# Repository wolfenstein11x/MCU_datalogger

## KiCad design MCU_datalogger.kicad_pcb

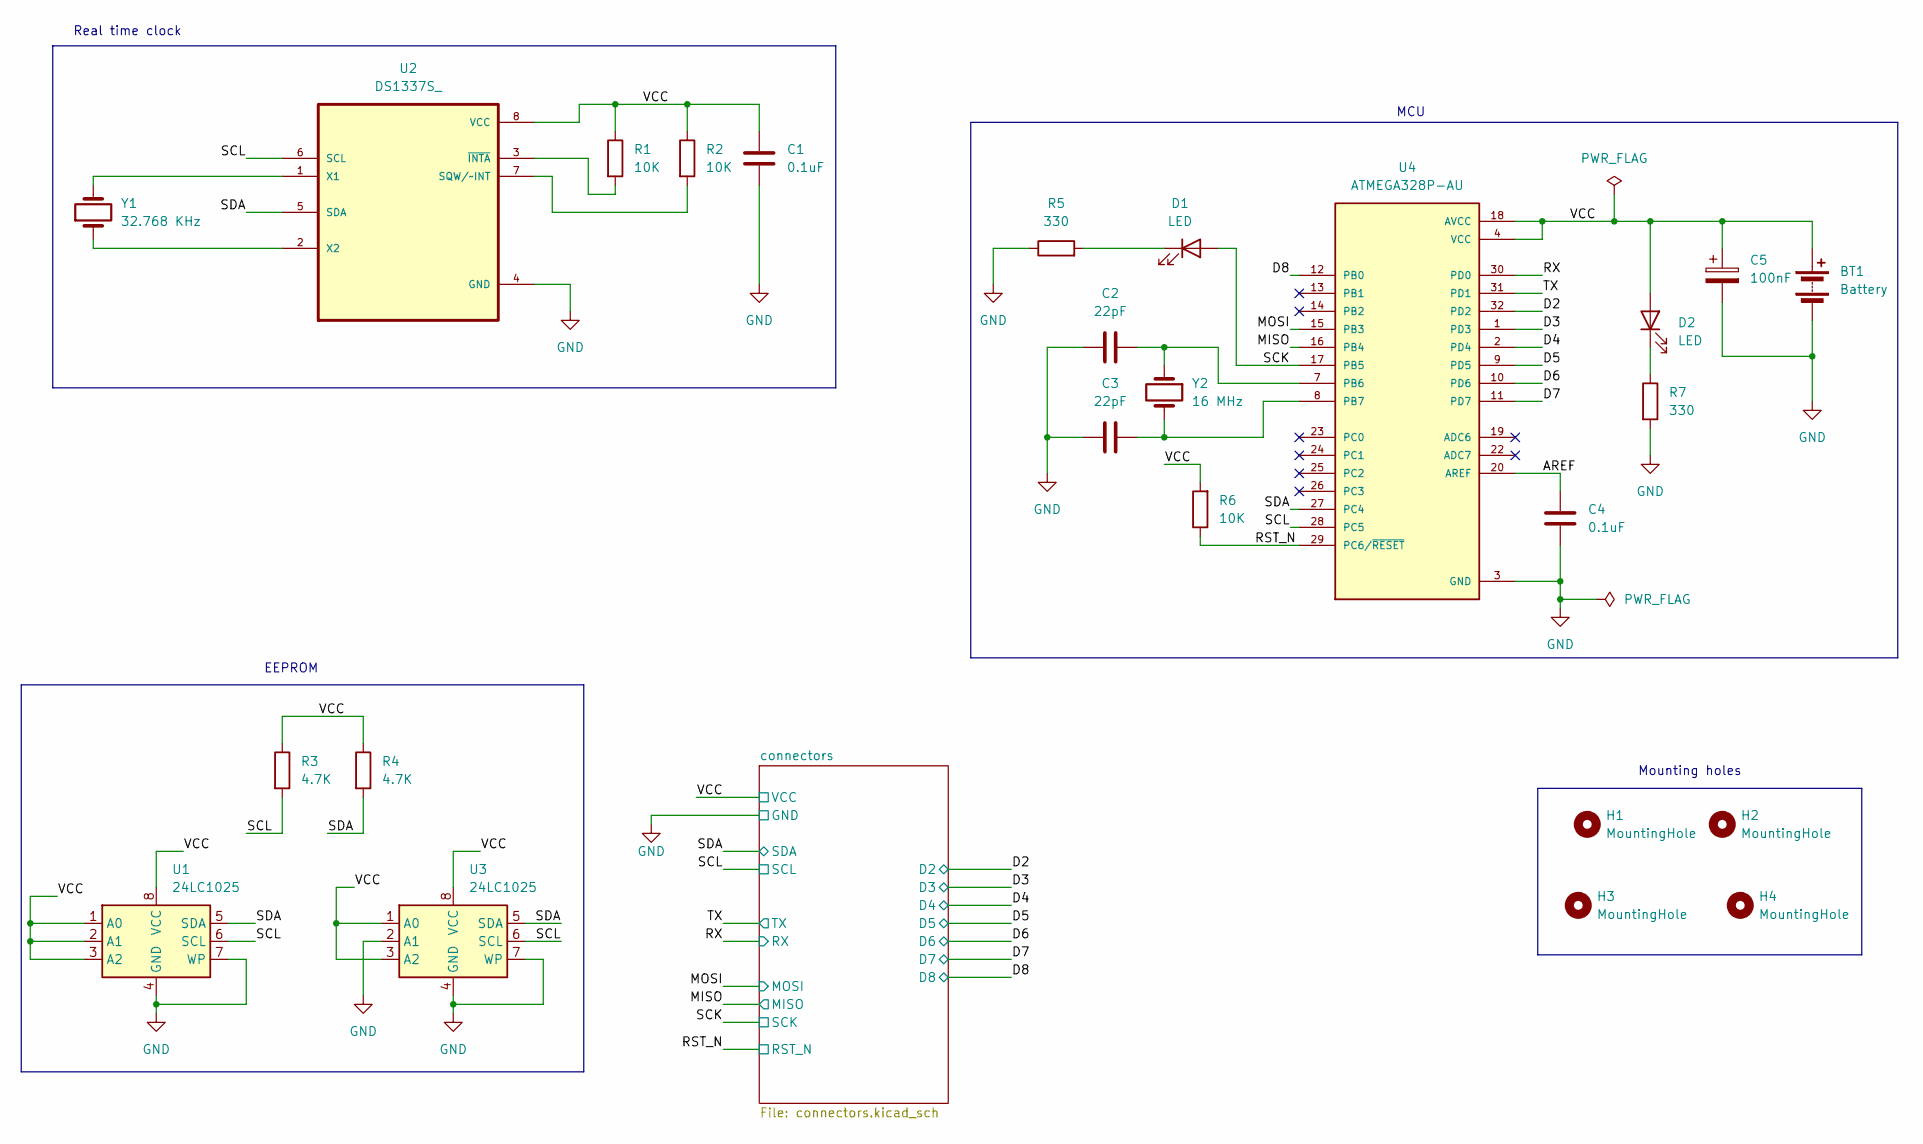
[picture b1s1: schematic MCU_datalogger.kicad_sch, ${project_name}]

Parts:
BT1: Battery; PinHeader_1x02_P2.54mm_Vertical
C1, C4: 0.1uF; C_0805_2012Metric
C2, C3: 22pF; C_0805_2012Metric
C5: 100nF; C_0805_2012Metric
D1, D2: LED; LED_0805_2012Metric
H1, H2, H3, H4: MountingHole; MountingHole_2.1mm
R1, R2, R6: 10K; R_0805_2012Metric
R3, R4: 4.7K; R_0805_2012Metric
R5, R7: 330; R_0805_2012Metric
U1, U3: 24LC1025; SOIC-8_5.23x5.23mm_P1.27mm
U2: DS1337S_; SOIC127P600X175-8N
U4: ATMEGA328P-AU; QFP80P900X900X120-32N; PARTREV 8271A
Y1: 32.768 KHz; Crystal_SMD_5032-2Pin_5.0x3.2mm_HandSoldering
Y2: 16 MHz; Crystal_SMD_5032-2Pin_5.0x3.2mm_HandSoldering

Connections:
/AREF: C4.2, U4.20 (AREF)
/D2: U4.32 (PD2); also elsewhere on the board
/D3: U4.1 (PD3); also elsewhere on the board
/D4: U4.2 (PD4); also elsewhere on the board
/D5: U4.9 (PD5); also elsewhere on the board
/D6: U4.10 (PD6); also elsewhere on the board
/D7: U4.11 (PD7); also elsewhere on the board
/D8: U4.12 (PB0); also elsewhere on the board
/MISO: U4.16 (PB4); also elsewhere on the board
/MOSI: U4.15 (PB3); also elsewhere on the board
/RST_N: R6.1, U4.29 (PC6/~RESET); also elsewhere on the board
/RX: U4.30 (PD0); also elsewhere on the board
/SCK: D1.2 (A), U4.17 (PB5); also elsewhere on the board
/SCL: R3.2, U1.6 (SCL), U2.6 (SCL), U3.6 (SCL), U4.28 (PC5); also elsewhere on the board
/SDA: R4.2, U1.5 (SDA), U2.5 (SDA), U3.5 (SDA), U4.27 (PC4); also elsewhere on the board
/TX: U4.31 (PD1); also elsewhere on the board
GND: BT1.2 (-), C1.2, C2.1, C3.1, C4.1, C5.2, R5.1, R7.2, U1.4 (GND), U1.7 (WP), U2.4 (GND), U3.2 (A1), U3.4 (GND), U3.7 (WP), U4.3 (GND), U4.5 (GND), U4.21 (GND); also elsewhere on the board
unnamed: D1.1 (K), R5.2
unnamed: D2.1 (K), R7.1
unnamed: R2.2, U2.7 (SQW/~INT)
unnamed: U2.1 (X1), Y1.2
unnamed: U2.2 (X2), Y1.1
unnamed: R1.2, U2.3 (~INTA)
unnamed: C2.2, U4.7 (PB6), Y2.1
unnamed: C3.2, U4.8 (PB7), Y2.2
VCC: BT1.1 (+), C1.1, C5.1, D2.2 (A), R1.1, R2.1, R3.1, R4.1, R6.2, U1.1 (A0), U1.2 (A1), U1.3 (A2), U1.8 (VCC), U2.8 (VCC), U3.1 (A0), U3.3 (A2), U3.8 (VCC), U4.4 (VCC), U4.6 (VCC), U4.18 (AVCC); also elsewhere on the board

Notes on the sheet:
EEPROM
Real time clock
Mounting holes
MCU

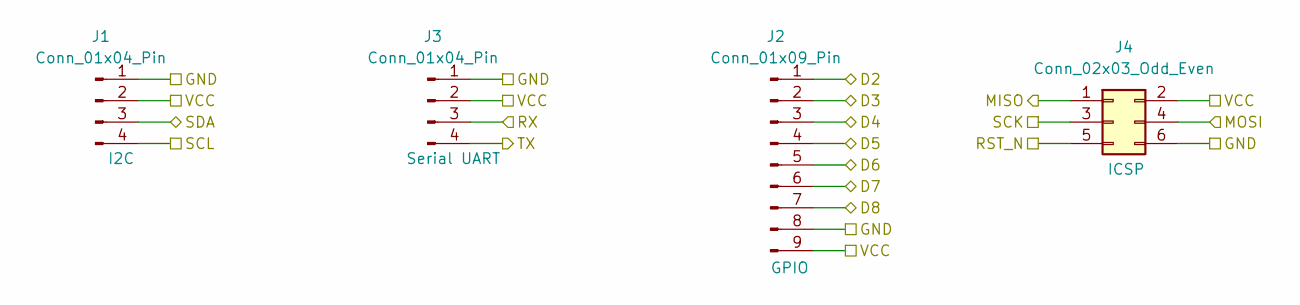
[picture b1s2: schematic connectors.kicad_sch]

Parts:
J1, J3: Conn_01x04_Pin; PinHeader_1x04_P2.54mm_Vertical
J2: Conn_01x09_Pin; PinHeader_1x09_P2.54mm_Vertical
J4: Conn_02x03_Odd_Even; PinHeader_2x03_P2.54mm_Vertical

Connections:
/D2: J2.1; also elsewhere on the board
/D3: J2.2; also elsewhere on the board
/D4: J2.3; also elsewhere on the board
/D5: J2.4; also elsewhere on the board
/D6: J2.5; also elsewhere on the board
/D7: J2.6; also elsewhere on the board
/D8: J2.7; also elsewhere on the board
/MISO: J4.1; also elsewhere on the board
/MOSI: J4.4; also elsewhere on the board
/RST_N: J4.5; also elsewhere on the board
/RX: J3.3; also elsewhere on the board
/SCK: J4.3; also elsewhere on the board
/SCL: J1.4; also elsewhere on the board
/SDA: J1.3; also elsewhere on the board
/TX: J3.4; also elsewhere on the board
GND: J1.1, J2.8, J3.1, J4.6; also elsewhere on the board
VCC: J1.2, J2.9, J3.2, J4.2; also elsewhere on the board

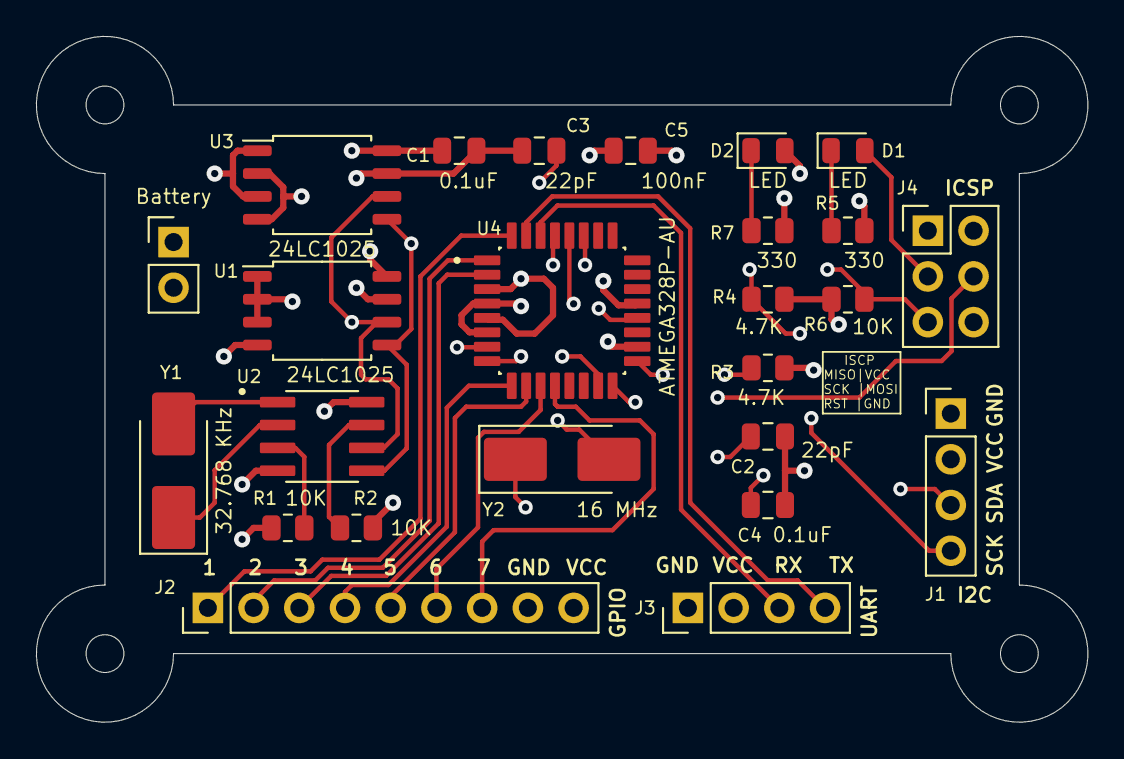
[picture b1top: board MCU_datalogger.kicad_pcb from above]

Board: 4 copper layers, 58.4 x 38.1 mm, 29 parts (0 on the bottom side), 26 nets.

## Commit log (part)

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2026-06-26 placed schematic parts
2026-06-30 assigned footpints in schematic
